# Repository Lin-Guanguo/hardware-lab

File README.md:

# Hardware Lab

用于个人硬件实验和小装置开发的 Git 仓库。每个装置放在 `projects/` 下，独立维护固件、硬件资料、依赖和构建流程。

## 当前确定方案

以下为各项目当前采用的方向；点击项目名查看最新文件和验证边界，历史方案保留在各项目后续章节。

| 项目 | 用途 | 最近记录的状态 |
| --- | --- | --- |
| [AI Passport](projects/ai-passport/README.md) | 探索紧凑的可编程胸牌、屏幕按键交互与 NFC 链接 | 2026-09-29 完成原厂 `trae_card 1.2.2` 的 8 MB 备份及设备校验，尚未更换固件 |
| [Image Oracle](projects/image-oracle/README.md) | 用固定算法将摄像头图像映射为答案，默认拍摄熔岩灯 | 2026-09-19 拼接原型完成并验收；后续探索更多传感器，或焊接、定制 PCB 与 3D 打印的紧凑装置 |
| [Programmable NFC Business Card](projects/nfc-business-card/README.md) | 按键切换身份的薄型 NFC 墨水屏名片 | 2026-09-28 决定在 `master` [重新规划 PCB](projects/nfc-business-card/docs/pcb-replan-2026-09-28.md)，DFM 约束前置，先验证新布局与关键区域试布；R21 和 6.3 mm 外壳候选保留作对照，尚不可投产。[PN532 桌面实测](projects/nfc-business-card/README.md#pn532-桌面测试程序)另行保留。 |

## 目录结构

```text
hardware-lab/
├── README.md
├── AGENTS.md
├── .gitignore
├── .gitmodules
├── .agents/
│   └── skills/
│       ├── easyeda-api -> ../../upstreams/easyeda-api-skill   <- 外部 Skill（符号链接）
│       ├── pcb-methodology/                                   <- 本仓库自建的方法论总控
│       └── kicad-workflow/                                    <- KiCad 备用工具执行与审查入口
├── upstreams/
│   ├── easyeda-api-skill/       <- 嘉立创 EDA 官方 API Skill（可调用）
│   ├── kicad-happy/             <- EMC 规则参考与按需 KiCad 分析脚本
│   ├── pcb-skill/               <- 同工具链的流程纪律与 MCP 陷阱（只读参考）
│   ├── pcba-design-skills/      <- 证据门禁与产物失效模型（只读参考）
│   ├── hw-review/               <- 逐引脚证据式审查、嘉立创 EDA 解析（只读参考）
│   ├── seeed-pn532/             <- PN532 NFC Type 4 模拟库（桌面测试依赖）
│   └── ndef/                    <- NDEF 消息编码库（桌面测试依赖）
├── eda/
│   ├── README.md
│   ├── NFC-Card-R1.eprj2
│   └── archive/              <- Historical native projects
├── docs/
│   ├── environment.md      <- 工具链、常驻服务、五分钟自检（新接手先看）
│   ├── pcb-design-rules.md <- DRC 看不见的规则：阈值、一手来源与本板适用性
│   ├── inventory.md
│   └── wiring-diagrams.md
└── projects/
    ├── ai-passport/
    │   ├── README.md
    │   └── docs/             <- 出厂固件备份与恢复记录
    ├── image-oracle/
    │   ├── README.md
    │   ├── firmware/
    │   ├── hardware/
    │   ├── scripts/
    │   ├── wiring-diagrams/
    │   └── docs/
    └── nfc-business-card/
        ├── README.md
        ├── firmware/         <- PN532 SPI 探测与固定网址 NDEF 测试程序
        ├── hardware/         <- production/r1/ 制造文件；records/ 校验证据
        ├── enclosure/        <- 模型、STEP/STL、报告；renders/ 是渲染图册
        ├── scripts/          <- 导出器、检查器、布线/线圈规划工具
        ├── wiring-diagrams/  <- PN532 与 ESP32-S3-CAM 交互式接线图
        ├── docs/             <- 含 progress.md 进度看板
        ├── archive/          <- 历史方案与旧索引
        └── artifacts/        <- 本机产物（全部忽略，只有 README.md 索引入库）
```

目录用途与命名约定见 [AGENTS.md](AGENTS.md)；本机环境、常驻服务与自检见 [环境与常驻服务](docs/environment.md)。所有目录均在首次有实际内容时创建；新项目可以只有 README，不使用占位文件预建目录。根目录 `docs/` 保存跨项目信息，包括器件清单和[接线图制作与归档方法](docs/wiring-diagrams.md)。

根目录 [eda/](eda/README.md) 直接保存嘉立创 EDA 的原始 `.eprj2` 工程，不使用工程文件符号链接；历史工程移到 `eda/archive/`。客户端只需登记一次 `hardware-lab/eda/`。正式工程纳入 Git，所属项目通过文档关联；BOM 等资料仍保存在项目的 `hardware/`，临时导出产物放在 `artifacts/`。

现有接线图见 [Image Oracle 图册](projects/image-oracle/wiring-diagrams/README.md)和[电子名片桌面实验图册](projects/nfc-business-card/wiring-diagrams/README.md)。后续默认使用带主板外形、完整丝印和模块排针数字序号的接线图；各项目使用相同目录名。

## 设计方法论

DRC 只证明几何没撞上，不证明设计正确。仓库级 [PCB 设计规则索引](docs/pcb-design-rules.md) 列出 DRC 看不见的规则、阈值、一手来源，以及每条规则对 2 层薄板的适用性；流程、约束层级与电气敏感件门禁见自建 skill [pcb-methodology](.agents/skills/pcb-methodology/SKILL.md)。

外部方法论仓库以 Git submodule 引入 `upstreams/`，按需跟随主线。分两类：可直接调用的 Skill 用符号链接进 `.agents/skills/`；只作参考的上游不加链接、不执行其脚本，由自建总控 skill 引用。上游的规则原文不复制进本仓库，引用时标注仓库、文件与规则编号。

KiCad 备用工具链通过本仓库 [kicad-workflow](.agents/skills/kicad-workflow/SKILL.md) 使用官方 IPC/CLI，并按需调用既有 `kicad-happy` 分析脚本；不全量安装上游流程。安装、自检和独立样例见 [tools/kicad](tools/kicad/README.md)。NFC 名片本轮仍使用嘉立创 EDA。

## 开始工作

0. 新机器/新接手先看[环境与常驻服务](docs/environment.md)：工具链路径、EDA 桥接（launchd）从零重建、五分钟自检清单与常见故障。
1. 阅读 [AGENTS.md](AGENTS.md) 和目标项目的 README。
2. 分配引脚和确定供电前，先核对实物及对应资料。
3. 改布局、布线、板框或器件位号前，先看 [PCB 设计规则索引](docs/pcb-design-rules.md)，并按敏感件门禁判断要动的器件属于哪一类。
4. 将固件放入项目的 `firmware/`，在项目 README 记录具体工具链、依赖版本和已验证的 shell 命令。
5. 先复现已知可用的例程，再修改应用功能。
6. 记录完成了哪些构建、哪些实机测试，以及仍未确认的事项。

各项目在自己的 README 记录已验证的构建、烧录与测试命令；在本地 Mac 上使用编辑器、shell 工具和 AI 辅助开发。

克隆后使用 `git submodule update --init --recursive` 初始化 `upstreams/` 下的外部仓库。外部 Skill 通过 `.agents/skills/` 中的相对符号链接供 Codex 发现；EDA Skill 的本地依赖与启动方式见 [软件说明](projects/nfc-business-card/docs/software.md)。

## 仓库约定

- 按装置或用途组织项目，每个项目可使用不同的 MCU 和工具链版本。
- 详细状态和下一步放在项目 README，根目录项目表仅作简要导航。
- Git 保存源码、实用的小型素材、可编辑 CAD、依赖锁文件和可复现配置。临时固件导出、采集数据和测量输出放入被忽略的 `artifacts/` 或 `logs/` 目录。
- ESP-IDF 的有意配置保存在 `sdkconfig.defaults` 及所需变体中；生成的 `sdkconfig` 和构建产物不入库。
- 外部上游仓库统一用 Git submodule 放在 `upstreams/`，固定提交并保留上游许可证，在项目文档记录 URL、revision 和使用方式。直接导入的例程仍需记录来源，避免把其嵌套 `.git` 目录复制进仓库。
- 文档默认使用中文；代码、代码注释和专有名词保持英文，具体见 [AGENTS.md](AGENTS.md) 的语言约定。

历史讨论和采购决策继续保存在 [CyberMnema](../CyberMnema/README.md)，通过链接关联。本仓库记录实际工程进展。

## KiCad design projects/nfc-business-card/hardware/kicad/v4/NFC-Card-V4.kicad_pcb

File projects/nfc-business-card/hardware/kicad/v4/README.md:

# NFC 名片 V4 KiCad 工程

## 当前确定方案

这是第四版的**迁移与关键区实际试布候选，不可制造**。完整结论、未完成项、回流图及国内 DFM 见 [阶段报告](../../kicad-v4-phase1.md)。先联合解决 VBUS／屏幕通道、参考地和电源输入，再决定整板详细设计。

用 KiCad 10.0.6 打开 [NFC-Card-V4.kicad_pro](NFC-Card-V4.kicad_pro)。项目包含根原理图和四张子页、PCB、规则、配置、符号库与 71 个使用中的封装变体；`fp-lib-table` / `sym-lib-table` 均用 `${KIPRJMOD}`，无需外部个人库。没有已验证的完整 STEP 装配模型。

保存重开已核对：66 个 BOM 位号、256 器件引脚、10 个板上触点，174 段铜线／22 个过孔；83 个未连接项是实际未完成。原理图／PCB parity 0、ERC 6、DRC 94，没有新增排除规则。

## 文件与证据

| 入口 | 用途 |
| --- | --- |
| `NFC-Card-V4.kicad_sch`、`1_…` 至 `4_…` | 全局标签连接的四页原理图；根页是导航 |
| `NFC-Card-V4.kicad_pcb` | 新试布，仅沿用 D 的 NFC 铜线；不是 D 全铜转换板 |
| `NFC-Card-V4.kicad_pro`、`.kicad_dru` | 双层／0.8 mm 与实际 DRC 规则 |
| `NFC_V4.kicad_sym`、`NFC_V4.pretty/` | 项目符号／封装；按实例保留非对称锡膏和开窗差异 |
| `placement-*.json`、`*-routing-spec*.json` | 本次各阶段决策／实际接受的几何；历史删除 UUID 不可直接用于新副本 |
| `reproduce-final-plan.json` | 从未清线的迁移基线，一次重放最终 38 个摆位、54 条路径／16 孔；目标是独立 `v4-replay/` |
| [最终验证](../../records/kicad-v4/final-validation.json)、[重开](../../records/kicad-v4/reopen.json) | 每个设计文件指纹、引脚与固定几何核对 |
| [制造诊断包](../../records/kicad-v4/dfm-diagnostic-02/README.md) | 含 D 旧铜的独立链路诊断，不能用于证明本试布的 DFM |

## 检查命令

从仓库根目录运行，使用已安装的 Python 几何库及现有 KiCad 工具链，不重新安装：

```sh
python3 tools/kicad/health.py
python3 projects/nfc-business-card/scripts/verify-v4-phase1.py
python3 projects/nfc-business-card/scripts/audit-v4-trial.py
```

后两条写入阶段验证记录和四张实际铜／地图片；它们针对当前冻结的第一阶段候选，不是任意新板的通用放行器。执行 ERC/DRC 的完整命令与预期非零结果在阶段报告中。

## 迁移与重放

实际导入顺序：KiCad Manager → File → Import Non-KiCad Project → EasyEDA Pro，选择 [D 交换文件](../../records/kicad-v4/NFC-Card-D-export.epro)，保存到全新的 `artifacts/kicad-v4/migration/native-import/`。导入后的基名为 `NFC-Card-D-export`，导入库为 `NFC-Card-D-easyedapro`；不要把 `.eprj2` 数据库送入这个入口。原始导入曾有跨页网络、禁铜区域与开口差异，必须再运行重建。

把 [D Gerber ZIP](../../records/board-review-d-diagnostic-gerber.zip)解压到新的 `artifacts/kicad-v4/migration/d-gerber/`。以下输出目录必须尚不存在；当前本机这些阶段已做过，不要覆盖它们：

```sh
python3 projects/nfc-business-card/scripts/migrate-v4-kicad.py --import-dir projects/nfc-business-card/artifacts/kicad-v4/migration/native-import --d-gerber-dir projects/nfc-business-card/artifacts/kicad-v4/migration/d-gerber --output projects/nfc-business-card/artifacts/kicad-v4/reconciled-d-REPLAY
python3 projects/nfc-business-card/scripts/prepare-v4-trial.py projects/nfc-business-card/artifacts/kicad-v4/reconciled-d-REPLAY projects/nfc-business-card/hardware/kicad/v4-replay
```

在 KiCad 打开 `v4-replay/NFC-Card-V4.kicad_pro` 及其 PCB Editor，再执行：

```sh
python3 tools/kicad/health.py --ipc --board /Users/linguanguo/dev/hardware-lab/projects/nfc-business-card/hardware/kicad/v4-replay/NFC-Card-V4.kicad_pcb
.cache/kicad-venv/bin/python projects/nfc-business-card/scripts/apply-v4-ipc.py projects/nfc-business-card/hardware/kicad/v4/reproduce-final-plan.json
```

脚本核对完整目标路径，只允许从 912 段／198 孔的未清线 D 基线执行首次清线，保留 NFC。关闭 PCB Editor，再恢复 IPC 可能扰动的导入封装局部图形：

```sh
python3 projects/nfc-business-card/scripts/finalize-v4-native.py projects/nfc-business-card/hardware/kicad/v4-replay projects/nfc-business-card/artifacts/kicad-v4/reconciled-d-REPLAY projects/nfc-business-card/artifacts/kicad-v4/migration/d-gerber projects/nfc-business-card/artifacts/kicad-v4/replay-finalize.json
```

最终原理图另外做了无连接线尾修复、原生 GUI 元数据规范化和根页排版；这些不改变网络。`clean-v4-schematic-stubs.py` 是本次固定目标、先后网表相同才保留的修复脚本，不能不改目标便拿去操作 replay。新副本必须独立开、保存、关、重开，执行 ERC/DRC/parity；不能把当前工程的验证计数移植给新副本。

上述聚合重放计划已和保存板的摆位及铜段／过孔数量核对；实际分阶段 IPC 操作及最终原生板已经验证，聚合计划未另开一次 GUI 全程重演，不宣称独立重演也已通过。

## 制造导出

仅在已保存、重新检查的同一版本导出。以下可用于当前未完成候选的**新诊断**；不会自动上传，更不能下单：

```sh
python3 projects/nfc-business-card/scripts/export-kicad-dfm.py projects/nfc-business-card/hardware/kicad/v4/NFC-Card-V4.kicad_pcb projects/nfc-business-card/artifacts/kicad-v4/dfm-NEW
```

输出同版 Gerber/钻孔 ZIP、BOM.csv、CPL.csv、原生位置表、钻孔报告和 SHA-256 manifest。脚本坚持冻结 D 的 66 件料号；以后若获授权改选型，必须先更新相应源数据／对账，不跳过断言。国内页面每次检查都需核对 0.8 mm 板厚和工艺字段，查看层、槽、关键器件方向及检查细目。

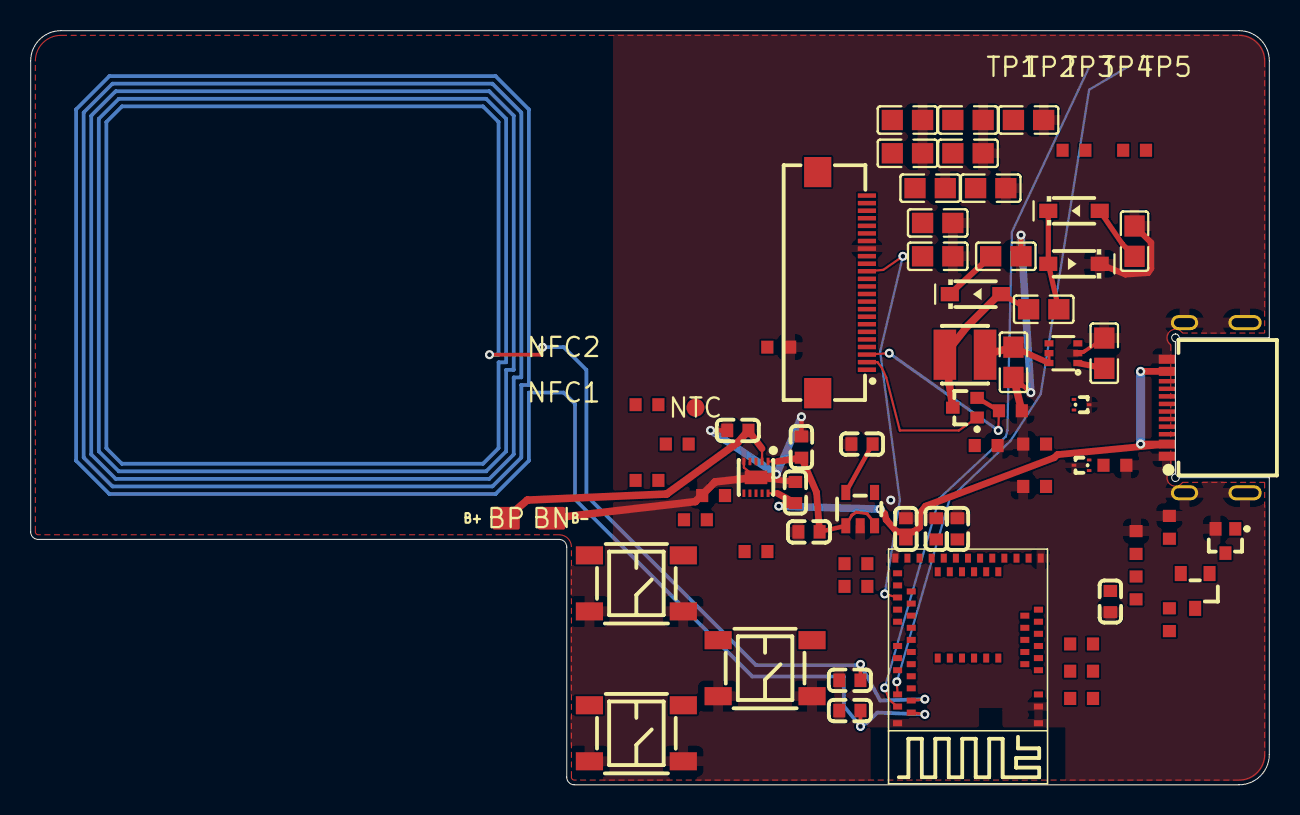
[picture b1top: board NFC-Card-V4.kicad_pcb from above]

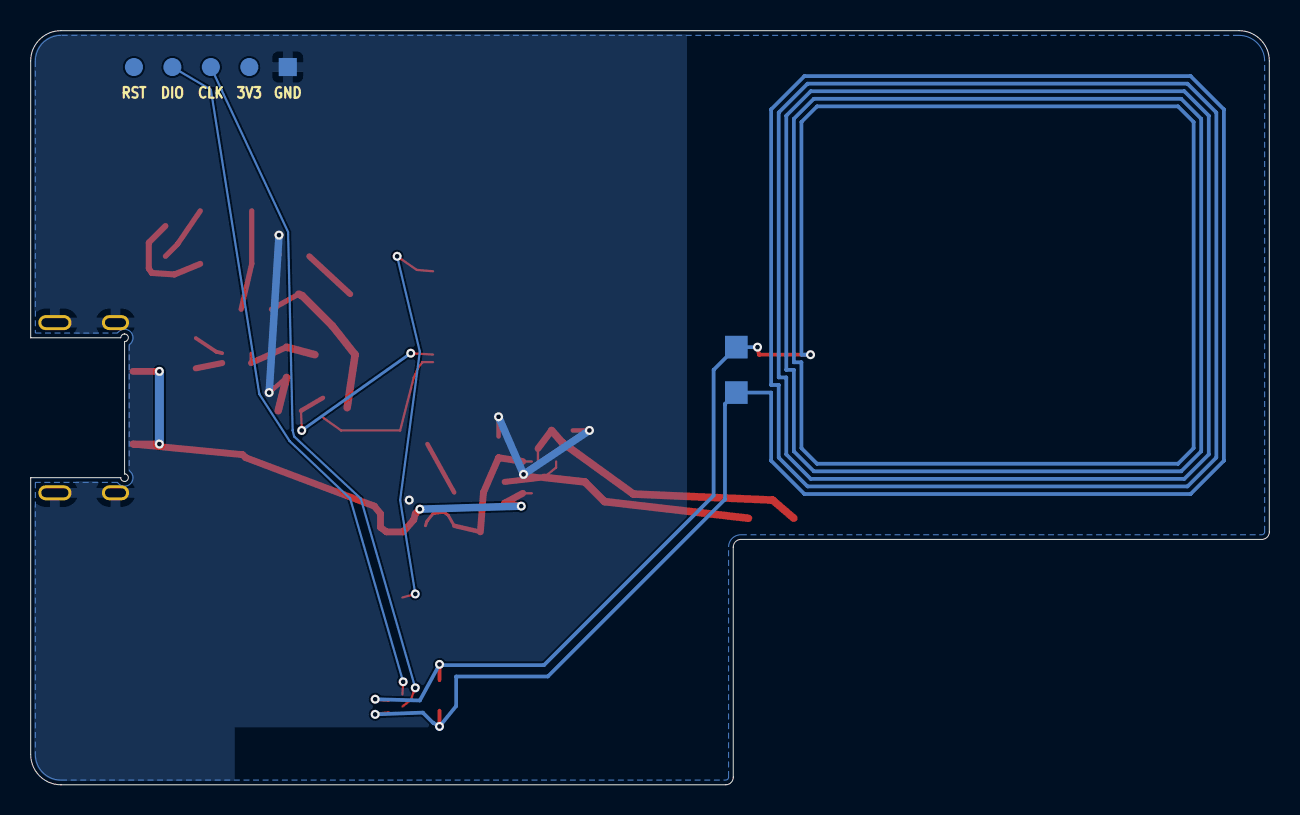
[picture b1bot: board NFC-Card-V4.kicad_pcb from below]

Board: 2 copper layers, 81.8 x 49.8 mm, 76 parts (7 on the bottom side), 52 nets.

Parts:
BN: PCB contact; Pad_e107
BP: PCB contact; Pad_e106
C1: 2.2uF 16V; C0603_C1
C2: 10uF 10V; C0603_C2
C3: 2.2uF 16V; C0603_C3
C4, C5: 2.2uF 16V; C0603
C6: 10uF 10V; C0603_C6
C7: 100nF 50V; C0603_C7
C8: 4.7uF 16V; C0603_C8
C9: 1uF; C0805_C9
C10, C13: 1uF; C0805
C11: 1uF; C0805_C11
C12: 1uF; C0805_C12
C14: 4.7uF; C0805_C14
C15: 4.7uF; C0805_C15
C16: 1uF; C0805_C16
C17: 1uF; C0805_C17
C18: 1uF; C0805_C18
C19: 4.7uF; C0805_C19
C20: 1uF; C0805_C20
C21: 1uF; C0805_C21
C22: 1uF; C0805_C22
C23: 220pF C0G (tune); C0603_C23
C24: 220pF C0G (tune); C0603_C24
C25: 100nF; C0603_C25
D1: MBR0530T1G; SOD-123_L2.7-W1.6-LS3.7-RD-1_D1
D2: MBR0530T1G; SOD-123_L2.7-W1.6-LS3.7-RD-1_D2
D3: MBR0530T1G; SOD-123_L2.7-W1.6-LS3.7-RD-1
J1: USB4500-03-0-A; USB-SMD_USB4500-03-0-A
J2: FPC-05FB-24PH20; FPC-SMD_24P-P0.50_FPC-05FB-24PH20
L1: 47uH; IND-SMD_L3.0-W3.0
NFC1: PCB contact; Pad_e245
NFC2: PCB contact; Pad_e246
NTC: PCB contact; Pad_e108
Q1: SI1308EDL-T1-GE3; SOT-323_L2.0-W1.3-P1.30-LS2.1-BR
Q2: AO3401A; SOT-23_L2.9-W1.3-P1.90-LS2.4-BR
Q3: SI1308EDL; SOT-323_L2.0-W1.3-P1.30-LS2.1-BR_Q3
R1: 5.1k 1%; R0603_R1
R2: 5.1k 1%; R0603_R2
R3: 0Ω; R0603_R3
R4: 0Ω; R0603_R4
R5: 10k 1%; R0603_R5
R6: 10k 1%; R0603_R6
R7: 10k 1%; R0603_R7
R8: 10k 1%; R0603_R8
R9: 10k 1%; R0603_R9
R10: 10k 1%; R0603_R10
R11: 10k 1%; R0603_R11
R12: 10k 1%; R0603_R12
R13: 100kΩ; R0603_R13
R14: 10kΩ; R0603_R14
R15: 2.2Ω; R0603_R15
R16: 0Ω; R0603_R16
R17: 3Ω; R0603_R17
R18: 10kΩ; R0603_R18
R19: 10k 1%; R0603_R19
R20, R21: 1MΩ; R0603
R22: 1MΩ; R0603_R22
R23: 1MΩ; R0603_R23
SW1, SW2, SW3: SKQGABE010; KEY-SMD_4P-L5.2-W5.2-P3.70-LS6.4
TP1: PCB contact; Pad_e101
TP2: PCB contact; Pad_e102
TP3: PCB contact; Pad_e103
TP4: PCB contact; Pad_e104
TP5: PCB contact; Pad_e105
U1: MDBT50Q-P1MV2; COMM-SMD_MDBT50Q-1MV2
U2: BQ25186DLHR; WSON-10_L2.2-W2.0-P0.40-BL-EP_TI_DLH0010A
U3: TPS7A0233DBVR; SOT-23-5_L2.9-W1.6-P0.95-LS2.8-BL
U4: TPS22919DCKT; SC-70-6_L2.0-W1.3-P0.65-LS2.1-BR
U5: TPD2EUSB30DRTR; SOT-9X3-3_L1.0-W0.8-P0.35-LS1.0-BR_U5
U6: TPD2EUSB30DRTR; SOT-9X3-3_L1.0-W0.8-P0.35-LS1.0-BR

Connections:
BAT_ADC_SENSE: C25.2, R20.1, R21.2, U1.11
BAT_DIV_SUPPLY: Q2.3, R20.2
BAT_MEAS_EN: Q3.1, R23.1, U1.10
BAT_NTC_TBD: NTC.1, R19.1, U2.6
BAT_PACK_TBD: BP.1, C3.1, Q2.2, R22.1, U2.2
BAT_SWITCH_GATE: Q2.1, Q3.3, R22.2
CHG_CE_N: R7.2, U1.22, U2.4
CHG_INT_N: R8.2, U1.20, U2.9
CHG_PG_N: R9.2, U1.21, U2.3
CHG_SCL: R6.2, U1.16, U2.8
CHG_SDA: R5.2, U1.19, U2.7
EPD_BS0: J2.8, R17.1
EPD_BUSY_TBD: J2.9, R18.2, U1.24
EPD_CS_N_TBD: J2.12, U1.38
EPD_DC_TBD: J2.11, U1.39
EPD_EN_TBD: R13.1, U1.27, U4.3
EPD_GDR: J2.2, Q1.1, R14.1
EPD_MOSI_TBD: J2.14, U1.37
EPD_PUMP: C11.2, D2.2, D3.1
EPD_RESE: J2.3, Q1.2, R15.1
EPD_RESET_N_TBD: J2.10, U1.41
EPD_SCK_TBD: J2.13, U1.36
EPD_SW: C11.1, D1.2, L1.2, Q1.3
EPD_VCOM: C22.1, J2.24
EPD_VDD: C10.1, J2.15, L1.1, R18.1, U4.5, U4.6
EPD_VDDL: C14.1, J2.4
EPD_VGH: J2.21, R16.2
EPD_VGL: C13.1, C21.1, D3.2, J2.23
EPD_VPH: C12.1, D1.1, R16.1
EPD_VSNH: C20.1, J2.22
EPD_VSNL1: C17.1, J2.18
EPD_VSNL2: C18.1, J2.19
EPD_VSPH: C19.1, J2.20
EPD_VSPL1: C15.1, J2.5
EPD_VSPL2: C16.1, J2.16
GND: BN.1, C1.2, C2.2, C3.2, C4.2, C5.2, C6.2, C7.2, C8.2, C9.2, C10.2, C12.2, C13.2, C14.2, C15.2, C16.2, C17.2, C18.2, C19.2, C20.2, C21.2, C22.2, C23.2, C24.2, C25.1, D2.1, J1.17, J1.18, J1.19, J1.20, J1.A1B12, J1.B1A12, J2.17, Q3.2, R1.2, R2.2, R13.2, R14.2, R15.2, R17.2, R19.2, R21.1, R23.2, SW1.3, SW1.4, SW2.3, SW2.4, SW3.3, SW3.4, TP1.1, U1.1, U1.2, U1.15, U1.33, U1.55, U2.5, U2.11, U3.2, U4.2, U5.3, U6.3
KEY_NEXT_N: R11.2, SW2.1, SW2.2, U1.4
KEY_OK_N: R12.2, SW3.1, SW3.2, U1.5
KEY_PREV_N: R10.2, SW1.1, SW1.2, U1.3
NFC1_TBD: C23.1, C24.1, NFC1.1, NFC2.1, U1.52, U1.54
NRESET: TP5.1, U1.40
SWDCLK: TP3.1, U1.53
SWDIO: TP4.1, U1.51
SYS: C2.1, C4.1, U2.1, U3.1, U3.3
USB_CC1: J1.A5, R1.1, U6.1
USB_CC2: J1.B5, R2.1, U6.2
USB_DM_CONN: J1.A7, J1.B7, R4.1, U5.2
USB_DM_MCU: R4.2, U1.34
USB_DP_CONN: J1.A6, J1.B6, R3.1, U5.1
USB_DP_MCU: R3.2, U1.35
USB_VBUS: C1.1, C8.1, J1.A4B9, J1.B4A9, U1.32, U2.10
VDD_3V3: C5.1, C6.1, C7.1, C9.1, R5.1, R6.1, R7.1, R8.1, R9.1, R10.1, R11.1, R12.1, TP2.1, U1.28, U1.30, U3.5, U4.1

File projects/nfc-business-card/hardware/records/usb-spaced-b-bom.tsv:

No.	Quantity	Comment	Designator	Footprint	Value	Manufacturer Part	Manufacturer	Supplier Part	Supplier
1	4	2.2uF 16V	C1,C3,C4,C5	C0603	2.2uF	CL10A225KO8NNNC	SAMSUNG(三星)	C23630	LCSC
2	2	10uF 10V	C2,C6	C0603	10uF	CL10A106KP8NNNC	SAMSUNG(三星)	C19702	LCSC
3	1	100nF 50V	C7	C0603	100nF	CC0603KRX7R9BB104	YAGEO(国巨)	C14663	LCSC
4	1	4.7uF 16V	C8	C0603	4.7uF	CL10A475KO8NNNC	SAMSUNG(三星)	C19666	LCSC
5	11	1uF	C9,C10,C11,C12,C13,C16,C17,C18,C20,C21,C22	C0805	1uF	CL21B105KBFNNNE	SAMSUNG(三星)	C28323	LCSC
6	3	4.7uF	C14,C15,C19	C0805	4.7uF	CL21B475KAFNNNE	SAMSUNG(三星)	C98195	LCSC
7	2	220pF C0G (tune)	C23,C24	C0603	220pF	GRM1885C1H221JA01D	muRata(村田)	C77032	LCSC
8	1	100nF	C25	C0603	100nF	CC0603KRX7R9BB104	YAGEO(国巨)	C14663	LCSC
9	3	MBR0530T1G	D1,D2,D3	SOD-123_L2.7-W1.6-LS3.7-RD-1		MBR0530T1G	onsemi(安森美)	C82046	LCSC
10	1	USB4500-03-0-A	J1	USB-SMD_USB4500-03-0-A		USB4500-03-0-A	GCT	C5354966	LCSC
11	1	FPC-05FB-24PH20	J2	FPC-SMD_24P-P0.50_FPC-05FB-24PH20		FPC-05FB-24PH20	XUNPU(讯普)	C2856831	LCSC
12	1	47uH	L1	IND-SMD_L3.0-W3.0	47uH	NRH3010T470MN	TAIYO YUDEN(太诱)	C223116	LCSC
13	1	SI1308EDL-T1-GE3	Q1	SOT-323_L2.0-W1.3-P1.30-LS2.1-BR		SI1308EDL-T1-GE3	VISHAY(威世)	C469327	LCSC
14	1	AO3401A	Q2	SOT-23_L2.9-W1.3-P1.90-LS2.4-BR	AO3401A	AO3401A	AOS	C15127	LCSC
15	1	SI1308EDL	Q3	SOT-323_L2.0-W1.3-P1.30-LS2.1-BR	SI1308EDL	SI1308EDL-T1-GE3	VISHAY(威世)	C469327	LCSC
16	2	5.1k 1%	R1,R2	R0603	5.1kΩ	0603WAF5101T5E	UNI-ROYAL(厚声)	C23186	LCSC
17	3	0Ω	R3,R4,R16	R0603	0Ω	0603WAF0000T5E	UNI-ROYAL(厚声)	C21189	LCSC
18	9	10k 1%	R5,R6,R7,R8,R9,R10,R11,R12,R19	R0603	10kΩ	0603WAF1002T5E	UNI-ROYAL(厚声)	C25804	LCSC
19	1	100kΩ	R13	R0603	100kΩ	0603WAF1003T5E	UNI-ROYAL(厚声)	C25803	LCSC
20	2	10kΩ	R14,R18	R0603	10kΩ	0603WAF1002T5E	UNI-ROYAL(厚声)	C25804	LCSC
21	1	2.2Ω	R15	R0603	2.2Ω	0603WAF220KT5E	UNI-ROYAL(厚声)	C22939	LCSC
22	1	3Ω	R17	R0603	3Ω	0603WAF300KT5E	UNI-ROYAL(厚声)	C23157	LCSC
23	4	1MΩ	R20,R21,R22,R23	R0603	1MΩ	0603WAF1004T5E	UNI-ROYAL(厚声)	C22935	LCSC
24	3	SKQGABE010	SW1,SW2,SW3	KEY-SMD_4P-L5.2-W5.2-P3.70-LS6.4		SKQGABE010	ALPSALPINE(阿尔卑斯阿尔派)	C115351	LCSC
25	1	MDBT50Q-P1MV2	U1	COMM-SMD_MDBT50Q-1MV2		MDBT50Q-P1MV2	RAYTAC	C5119772	LCSC
26	1	BQ25186DLHR	U2	WSON-10_L2.2-W2.0-P0.40-BL-EP_TI_DLH0010A		BQ25186DLHR	TI(德州仪器)	C44639442	LCSC
27	1	TPS7A0233DBVR	U3	SOT-23-5_L2.9-W1.6-P0.95-LS2.8-BL		TPS7A0233DBVR	TI(德州仪器)	C5142805	LCSC
28	1	TPS22919DCKT	U4	SC-70-6_L2.0-W1.3-P0.65-LS2.1-BR		TPS22919DCKT	TI(德州仪器)	C2860814	LCSC
29	2	TPD2EUSB30DRTR	U5,U6	SOT-9X3-3_L1.0-W0.8-P0.35-LS1.0-BR		TPD2EUSB30DRTR	TI(德州仪器)	C97502	LCSC
